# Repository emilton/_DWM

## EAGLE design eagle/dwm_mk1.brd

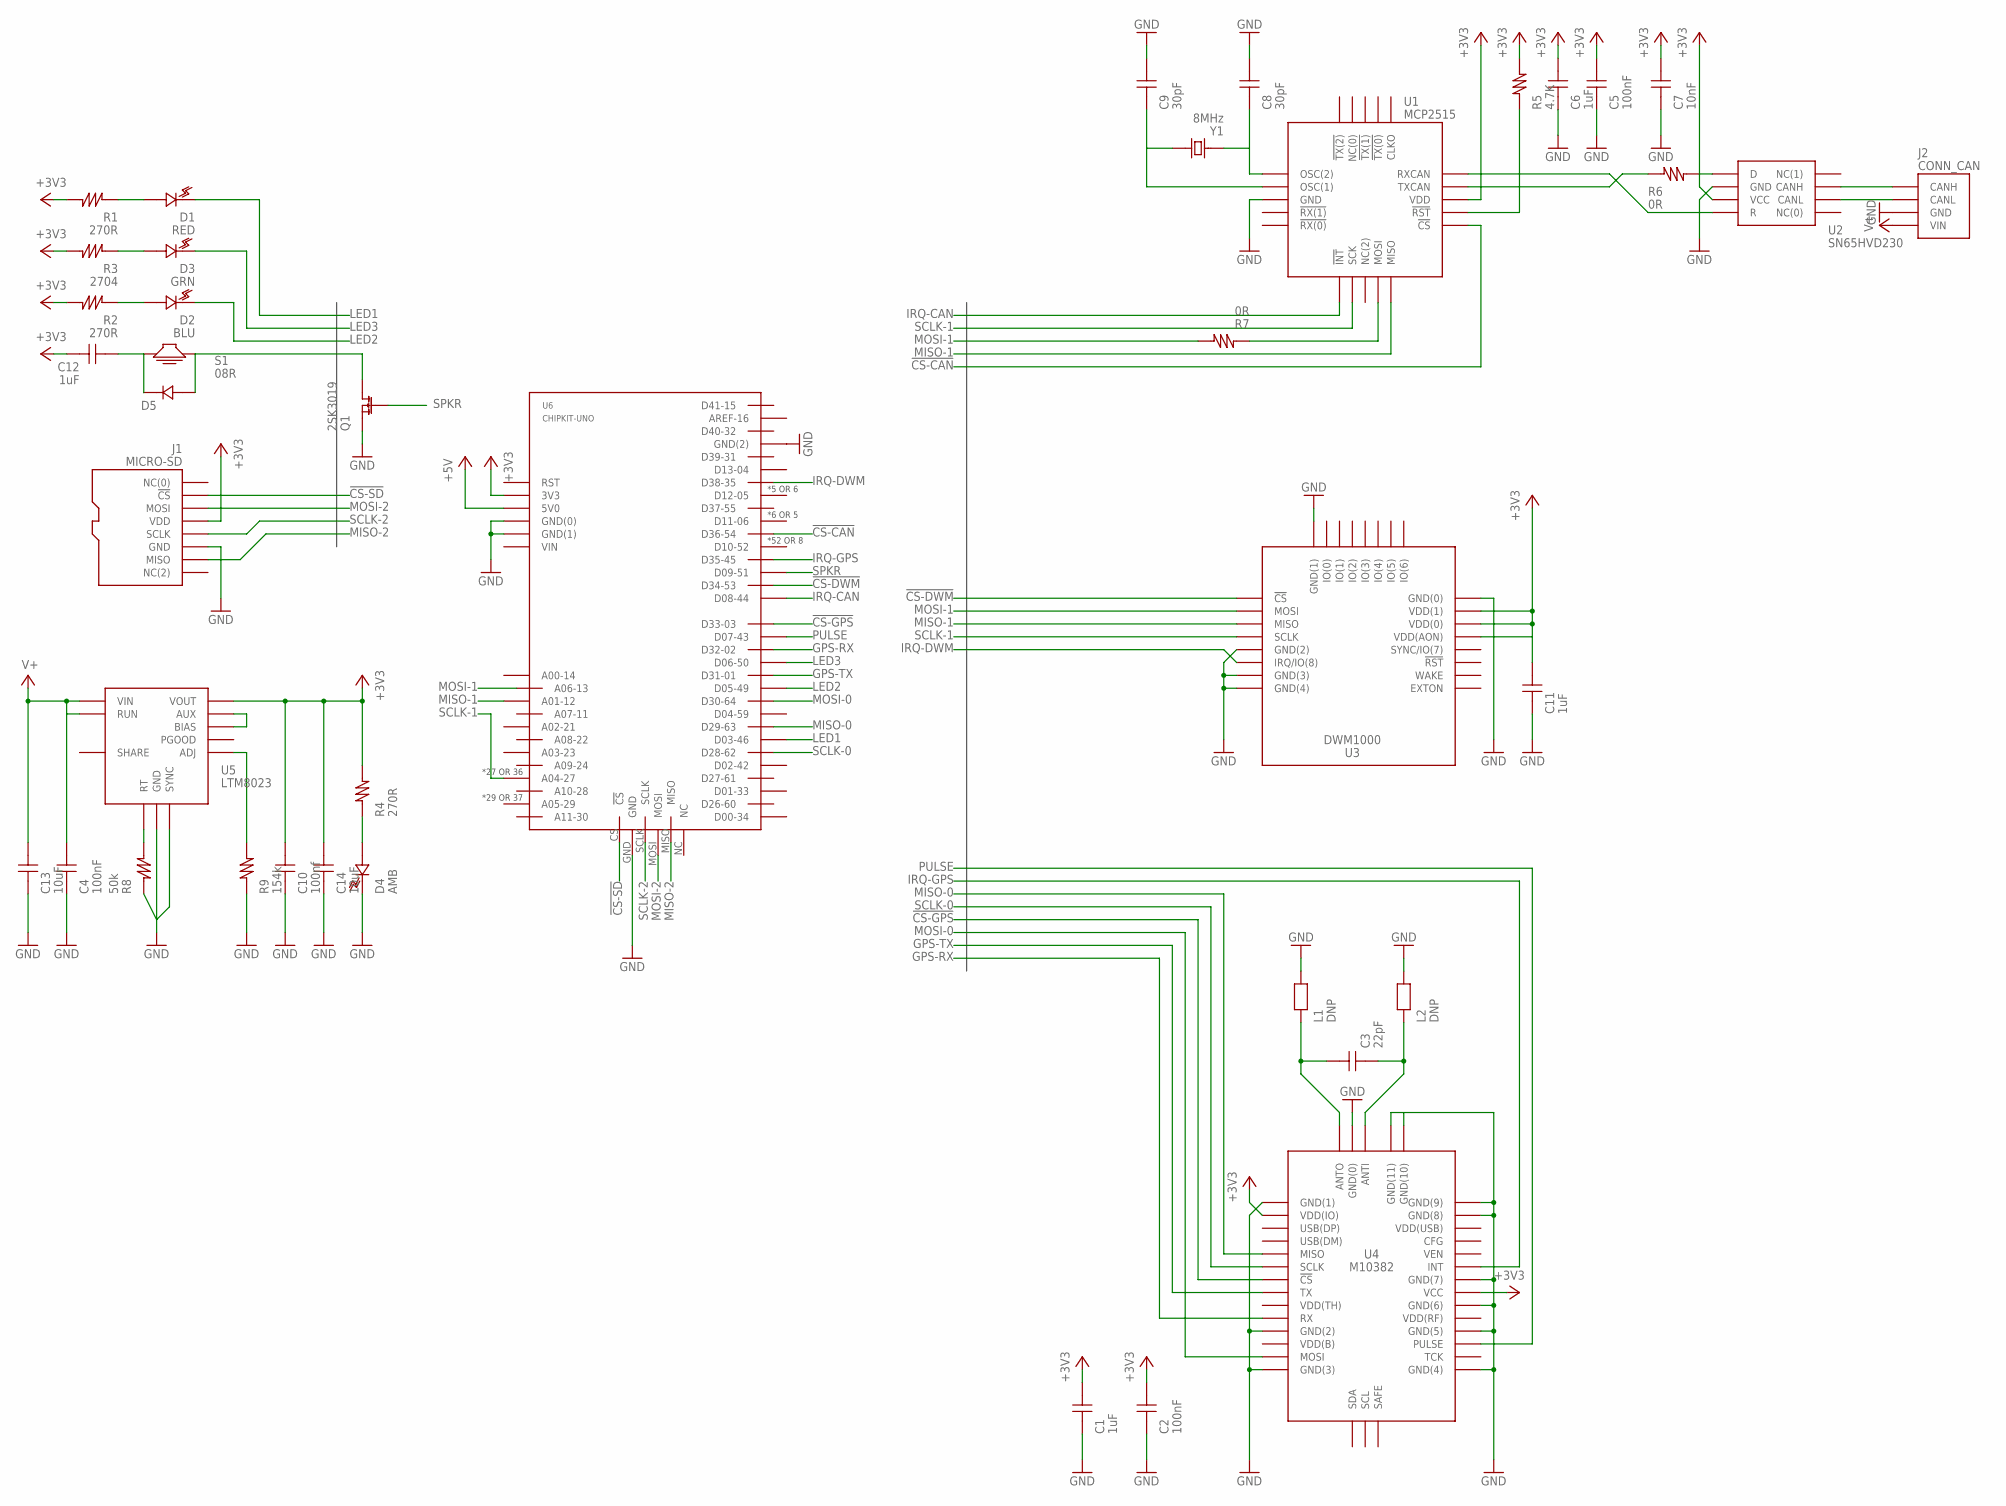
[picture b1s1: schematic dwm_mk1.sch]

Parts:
C1, C6, C11, C12: 1uF; E_0603@1
C2, C4, C5: 100nF; E_0603@1
C3: 22pF; E_0603@1
C7: 10nF; E_0603@1
C8, C9: 30pF; E_0603@1
C10: 100nf; E_0603@1
C13, C14: 10uF; E_1206@1
D1: RED; E_0603@1
D2: BLU; E_0603@1
D3: GRN; E_0603@1
D4: AMB; E_0603@1
D5: DIODE; E_0603@1
J1: MICRO-SD; SMT_MICROSD
J2: CONN_CAN; CON_4PIN
L1, L2: DNP; E_0603@1
Q1: 2SK3019; E_SOT416
R1, R2, R4: 270R; E_0603@1
R3: 2704; E_0603@1
R5: 4.7K; E_0603@1
R6, R7: 0R; E_0603@1
R8: 50k; E_0603@1
R9: 154k; E_0603@1
S1: 08R; SMT_BUZZER
U1: MCP2515; E_QFN20
U2: SN65HVD230; E_SOIC8
U3: DWM1000; DEC_DWM1000
U4: M10382; ANT_M10382
U5: LTM8023; LTM_8023
U6: CHIPKIT-UNO; MCP_CHIPKITUNO
Y1: 8MHz; CTS_CRYSTAL

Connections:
!CS-CAN: U1.P$16 (!CS), U6.D36 (D36-54)
!CS-DWM: U3.P$17 (!CS), U6.D34 (D34-53)
!CS-GPS: U4.P$10 (!CS), U6.D33 (D33-03)
!CS-SD: J1.P$2 (!CS), U6.CS (!CS)
+3V3: C1.P$1, C2.P$1, C5.P$1, C6.P$1, C7.P$1, C10.P$1, C11.P$1, C12.P$1, C14.P$1, J1.P$4 (VDD), R1.P$1, R2.P$1, R3.P$1, R4.P$1, R5.P$1, U1.P$18 (VDD), U2.P$3 (VCC), U3.P$5 (VDD(AON)), U3.P$6 (VDD(0)), U3.P$7 (VDD(1)), U4.P$5 (VDD(IO)), U4.P$27 (VCC), U5.A1 (VOUT), U5.A2 (VOUT), U5.A3 (VOUT), U5.A4 (VOUT), U5.B1 (VOUT), U5.B2 (VOUT), U5.B3 (VOUT), U5.B4 (VOUT), U5.C1 (VOUT), U5.C2 (VOUT), U5.C3 (VOUT), U5.C4 (VOUT), U6.3V3
+5V: U6.5V0
GND: C1.P$2, C2.P$2, C4.P$2, C5.P$2, C6.P$2, C7.P$2, C8.P$1, C9.P$1, C10.P$2, C11.P$2, C13.P$2, C14.P$2, D4.P$2, J1.P$6 (GND), J2.P$3 (GND), L1.P$1, L2.P$1, Q1.P$1 (SOURCE), R8.P$2, R9.P$2, U1.P$8 (GND), U2.P$2 (GND), U3.P$8 (GND(0)), U3.P$16 (GND(1)), U3.P$21 (GND(2)), U3.P$23 (GND(3)), U3.P$24 (GND(4)), U4.P$2 (GND(0)), U4.P$4 (GND(1)), U4.P$14 (GND(2)), U4.P$17 (GND(3)), U4.P$21 (GND(4)), U4.P$24 (GND(5)), U4.P$26 (GND(6)), U4.P$28 (GND(7)), U4.P$33 (GND(8)), U4.P$34 (GND(9)), U4.P$35 (GND(10)), U4.P$36 (GND(11)), U5.A5 (GND), U5.A6 (GND), U5.A7 (GND), U5.B5 (GND), U5.B6 (GND), U5.B7 (GND), U5.C5 (GND), U5.C6 (GND), U5.C7 (GND), U5.D1 (GND), U5.D2 (GND), U5.D3 (GND), U5.D4 (GND), U5.D5 (GND), U5.D6 (GND), U5.D7 (GND), U5.E1 (GND), U5.E2 (GND), U5.E3 (GND), U5.E4 (GND), U5.E5 (GND), U5.E6 (GND), U5.E7 (GND), U5.F6 (GND), U5.G6 (SYNC), U6.GND, U6.GND(0), U6.GND(1), U6.GND(2)
GPS-RX: U4.P$13 (RX), U6.D32 (D32-02)
GPS-TX: U4.P$11 (TX), U6.D31 (D31-01)
IRQ-CAN: U1.P$11 (!INT), U6.D08 (D08-44)
IRQ-DWM: U3.P$22 (IRQ/IO(8)), U6.D38 (D38-35)
IRQ-GPS: U4.P$29 (INT), U6.D35 (D35-45)
LED1: D1.P$2, U6.D03 (D03-46)
LED2: D2.P$2, U6.D05 (D05-49)
LED3: D3.P$2, U6.D06 (D06-50)
MISO-0: U4.P$8 (MISO), U6.D29 (D29-63)
MISO-1: U1.P$15 (MISO), U3.P$19 (MISO), U6.A01 (A01-12)
MISO-2: J1.P$7 (MISO), U6.MISO
MOSI-0: U4.P$16 (MOSI), U6.D30 (D30-64)
MOSI-1: R7.P$1, U3.P$18 (MOSI), U6.A06 (A06-13)
MOSI-2: J1.P$3 (MOSI), U6.MOSI
unnamed: C3.P$1, L1.P$2, U4.P$3 (ANTO)
unnamed: C3.P$2, L2.P$2, U4.P$1 (ANTI)
unnamed: D1.P$1, R1.P$2
unnamed: D3.P$1, R3.P$2
unnamed: R5.P$2, U1.P$17 (!RST)
unnamed: C12.P$2, D5.P$2, S1.P$1
unnamed: R6.P$1, U2.P$1 (D)
unnamed: R8.P$1, U5.G7 (RT)
unnamed: R6.P$2, U1.P$19 (TXCAN)
unnamed: U1.P$20 (RXCAN), U2.P$4 (R)
unnamed: R7.P$2, U1.P$14 (MOSI)
unnamed: C8.P$2, U1.P$6 (OSC(2)), Y1.P$3
unnamed: C9.P$2, U1.P$7 (OSC(1)), Y1.P$1
unnamed: R9.P$1, U5.H7 (ADJ)
unnamed: U5.F5 (AUX), U5.G5 (BIAS)
unnamed: D5.P$1, Q1.P$3 (DRAIN), S1.P$4
unnamed: D4.P$1, R4.P$2
unnamed: J2.P$1 (CANH), U2.P$7 (CANH)
unnamed: J2.P$2 (CANL), U2.P$6 (CANL)
PULSE: U4.P$23 (PULSE), U6.D07 (D07-43)
R2: D2.P$1, R2.P$2
SCLK-0: U4.P$9 (SCLK), U6.D28 (D28-62)
SCLK-1: U1.P$12 (SCK), U3.P$20 (SCLK), U6.A04 (A04-27)
SCLK-2: J1.P$5 (SCLK), U6.SCLK
SPKR: Q1.P$2 (GATE), U6.D09 (D09-51)
V+: C4.P$1, C13.P$1, J2.P$4 (VIN), U5.G1 (VIN), U5.G2 (VIN), U5.G3 (VIN), U5.H1 (VIN), U5.H2 (VIN), U5.H3 (VIN), U5.H5 (RUN)

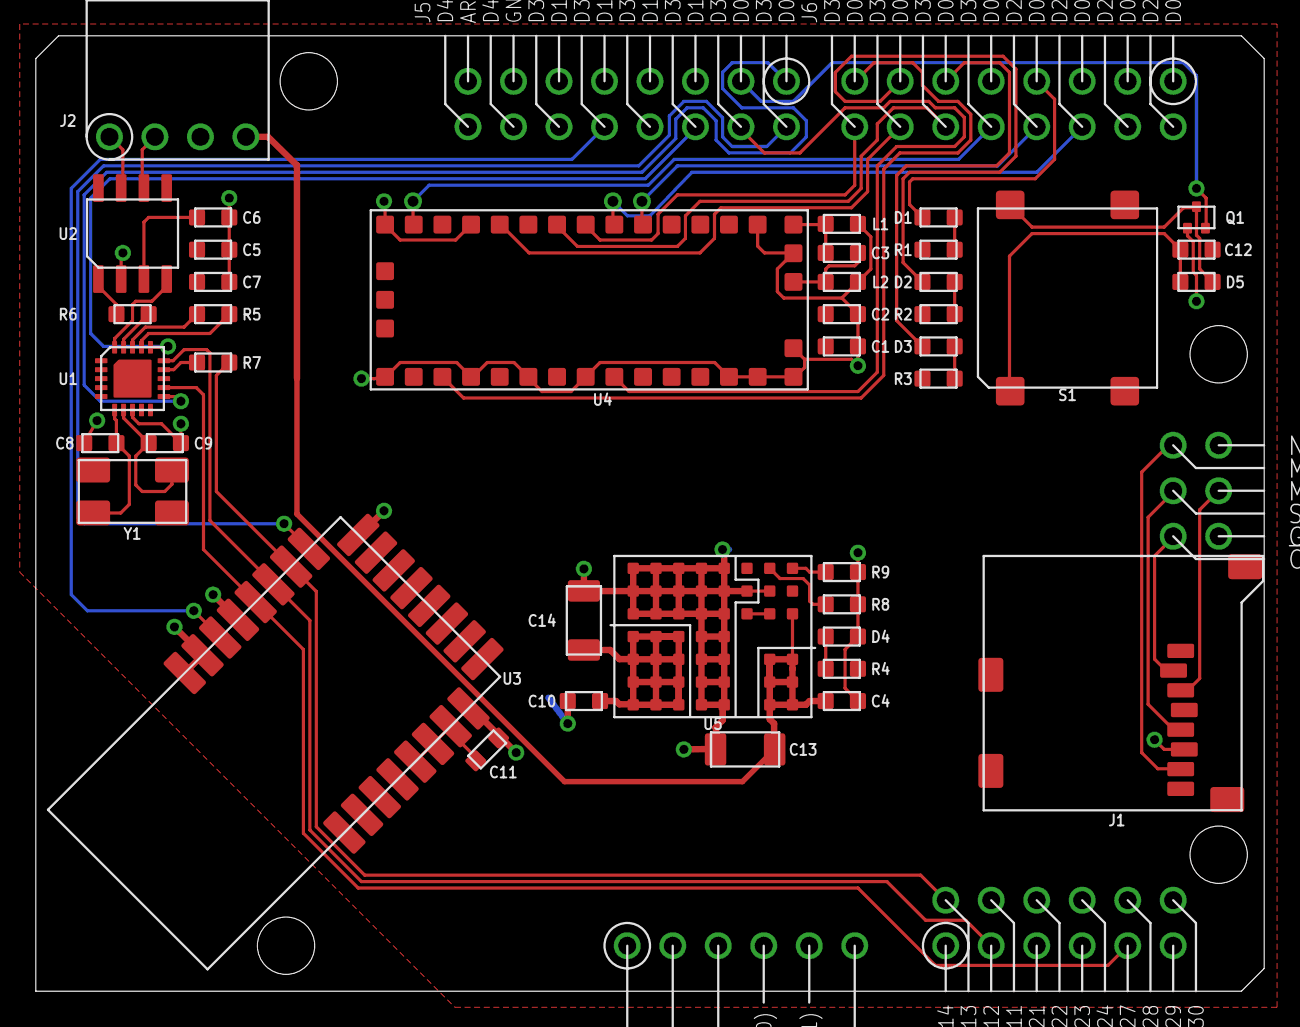
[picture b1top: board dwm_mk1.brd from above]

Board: 2 copper layers, 68.6 x 53.3 mm, 41 parts (0 on the bottom side), 46 nets.

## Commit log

2015-01-28 first commit
    DWM board is done, maybe a few minor tweaks before sending to OSH
2015-02-25 Finished board. Few minor changes to be made
